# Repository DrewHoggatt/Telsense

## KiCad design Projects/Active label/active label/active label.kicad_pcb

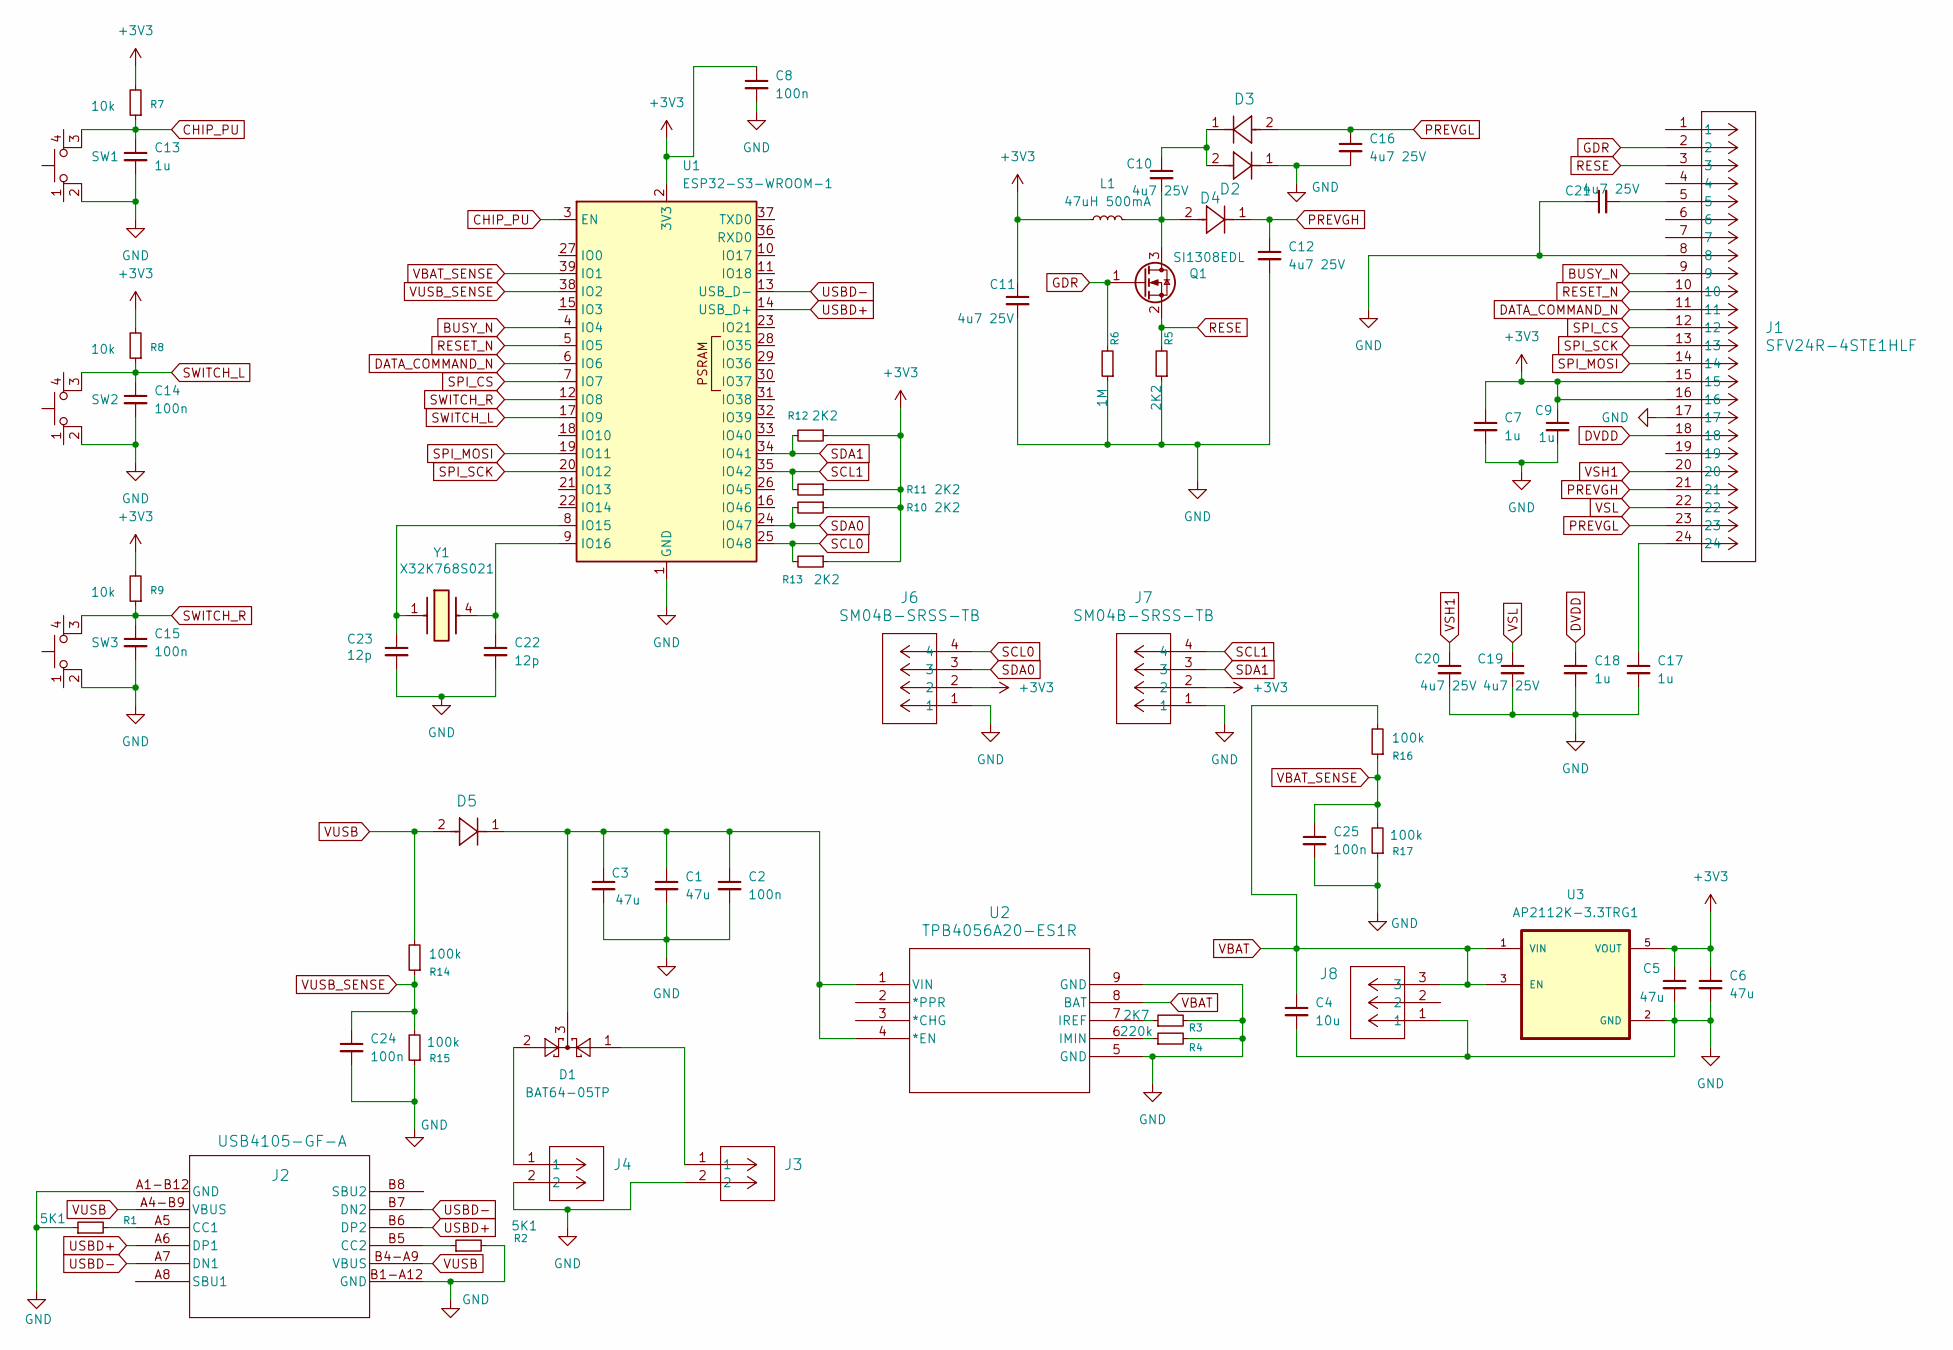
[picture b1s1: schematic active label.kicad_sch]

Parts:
C1, C3, C5, C6: 47u; C_0805_2012Metric; ManufacturerPN CL21A476MQYNNNE
C2, C8, C14, C15, C24, C25: 100n; C_0805_2012Metric; ManufacturerPN C0805X7R100-104KNE-CT
C4: 10u; C_0805_2012Metric; ManufacturerPN GRM21BC80J106KE19L
C7, C9, C13, C17, C18: 1u; C_0805_2012Metric; ManufacturerPN GRM219C8YA105KA73D
C10, C11, C12, C16, C19, C20, C21: 4u7 25V; C_0805_2012Metric; ManufacturerPN GRM219R6YA475MA73D
C22, C23: 12p; C_0805_2012Metric; ManufacturerPN CC0805JRNPO9BN120
D1: BAT64-05TP; SOT-323_SC-70; ManufacturerPN BAT64-05TP
D2, D3, D4, D5: SD0805S020S1R0; SD0805_AVX; ManufacturerPN SD0805S020S1R0
J1: SFV24R-4STE1HLF; CONN24_SFV24R-4STE1HLF_AMP; ManufacturerPN SFV24R-4STE1HLF
J2: USB4105-GF-A; USB4105_GCT
J3, J4: SM02B-SRSS-TB LFSN; CONN_SM02B-SRSS-TB_JST; ManufacturerPN SM02B-SRSS-TB
J6, J7: SM04B-SRSS-TB; CONN_SM04B-SRSS-TB_JST; ManufacturerPN SM04B-SRSS-TB
J8: SM03B-SRSS-TBLFSN; CONN_SM03B-SRSS-TB_JST; ManufacturerPN SM03B-SRSS-TB
L1: 47uH 500mA; IND_BOURNS_SRN8040; ManufacturerPN SRN8040-470M
Q1: SI1308EDL; SOT-23; ManufacturerPN SI1308EDL-T1-GE3
R1, R2: 5K1; R_0805_2012Metric; ManufacturerPN ESR10EZPF5101
R3: 2K7; R_0805_2012Metric; ManufacturerPN ESR10EZPF2701
R4: 220k; R_0805_2012Metric; ManufacturerPN ESR10EZPF2203
R5, R10, R11, R12, R13: 2K2; R_0805_2012Metric; ManufacturerPN ESR10EZPF2201
R6: 1M; R_0805_2012Metric; ManufacturerPN ESR10EZPF1004
R7, R8, R9: 10k; R_0805_2012Metric; ManufacturerPN ESR10EZPF1002
R14, R15, R16, R17: 100k; R_0805_2012Metric; ManufacturerPN ESR10EZPF1003
SW1, SW2, SW3: SW_MEC_5E; PTS526_08_CNK; ManufacturerPN PTS526-SK15J-SMTR
U1: ESP32-S3-WROOM-1; ManufacturerPN ESP32-S3-WROOM-1U-N8R8
U2: TPB4056A20-ES1R; ESOP-8_TPK; ManufacturerPN TPB4056A20-ES1R
U3: AP2112K-3.3TRG1; SOT95P285X140-5N; PARTREV 2-2
Y1: X32K768S021; Manufacturer_Part_Number X32K768S021

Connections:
+3V3: C5.1, C6.1, C7.1, C8.1, C9.1, C11.1, J1.15, J1.16, J6.2, J7.2, L1.1, R7.2, R8.2, R9.2, R10.1, R11.1, R12.1, R13.1, U1.2 (3V3), U3.5 (VOUT)
BUSY_N: J1.9, U1.4 (IO4)
CHIP_PU: C13.1, R7.1, SW1.3 (K), U1.3 (EN)
DATA_COMMAND_N: J1.11, U1.6 (IO6)
DVDD: C18.1, J1.18
GDR: J1.2, Q1.1 (G), R6.2
GND: C1.2, C2.2, C3.2, C4.2, C5.2, C6.2, C7.2, C8.2, C9.2, C11.2, C12.2, C13.2, C14.2, C15.2, C16.2, C17.2, C18.2, C19.2, C20.2, C21.1, C22.2, C23.2, C24.2, C25.2, D2.1, J1.8, J1.17, J2.A1-B12 (GND), J2.B1-A12 (GND), J3.2, J4.2, J6.1, J7.1, J8.1, R1.1, R2.2, R3.2, R4.2, R5.1, R6.1, R15.1, R17.1, SW1.2, SW2.2, SW3.2, U1.1 (GND), U1.40 (GND), U1.41 (GND), U2.5 (GND), U2.9 (GND), U3.2 (GND)
unnamed: C10.1, D2.2, D3.1
unnamed: C17.1, J1.24
unnamed: C21.2, J1.5
unnamed: D1.1, J3.1
unnamed: D1.2, J4.1
unnamed: J2.A5 (CC1), R1.2
unnamed: J2.B5 (CC2), R2.1
unnamed: C10.2, D4.2, L1.2, Q1.3 (D)
unnamed: C23.1, U1.8 (IO15), Y1.1
unnamed: C22.1, U1.9 (IO16), Y1.4
unnamed: C1.1, C2.1, C3.1, D1.3, D5.1, U2.1 (VIN), U2.4 (*EN)
unnamed: R4.1, U2.6 (IMIN)
unnamed: R3.1, U2.7 (IREF)
PREVGH: C12.1, D4.1, J1.21
PREVGL: C16.1, D3.2, J1.23
RESE: J1.3, Q1.2 (S), R5.2
RESET_N: J1.10, U1.5 (IO5)
SCL0: J6.4, R13.2, U1.25 (IO48)
SCL1: J7.4, R11.2, U1.35 (IO42)
SDA0: J6.3, R10.2, U1.24 (IO47)
SDA1: J7.3, R12.2, U1.34 (IO41)
SPI_CS: J1.12, U1.7 (IO7)
SPI_MOSI: J1.14, U1.19 (IO11)
SPI_SCK: J1.13, U1.20 (IO12)
SWITCH_L: C14.1, R8.1, SW2.3 (K), U1.17 (IO9)
SWITCH_R: C15.1, R9.1, SW3.3 (K), U1.12 (IO8)
USBD+: J2.A6 (DP1), J2.B6 (DP2), U1.14 (USB_D+)
USBD-: J2.A7 (DN1), J2.B7 (DN2), U1.13 (USB_D-)
VBAT: C4.1, J8.3, R16.2, U2.8 (BAT), U3.1 (VIN), U3.3 (EN)
VBAT_SENSE: C25.1, R16.1, R17.2, U1.39 (IO1)
VSH1: C20.1, J1.20
VSL: C19.1, J1.22
VUSB: D5.2, J2.A4-B9 (VBUS), J2.B4-A9 (VBUS), R14.2
VUSB_SENSE: C24.1, R14.1, R15.2, U1.38 (IO2)

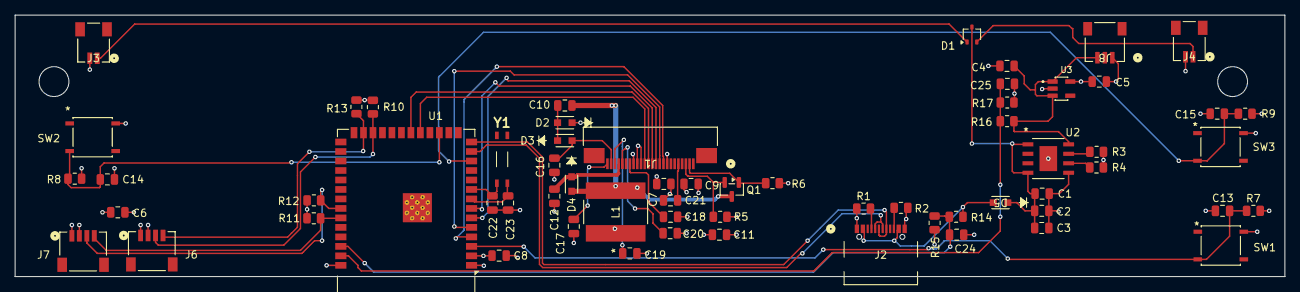
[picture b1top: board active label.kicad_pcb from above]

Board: 4 copper layers, 170.0 x 35.0 mm, 63 parts (0 on the bottom side), 41 nets.

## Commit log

2025-10-03 First experiments
2025-10-10 Lamp designs
2025-10-20 lamp work
2025-11-14 Timegrapher
2025-12-18 ESP32 experiment. Yuk!
2026-01-19 Add 3d Render Project
2026-01-20 Removed
2026-01-20 Removal
2026-03-24 Added BT HTML
2026-04-04 Active label
2026-04-05 Layout under way
2026-04-06 Board layout complete
2026-06-08 active label work
